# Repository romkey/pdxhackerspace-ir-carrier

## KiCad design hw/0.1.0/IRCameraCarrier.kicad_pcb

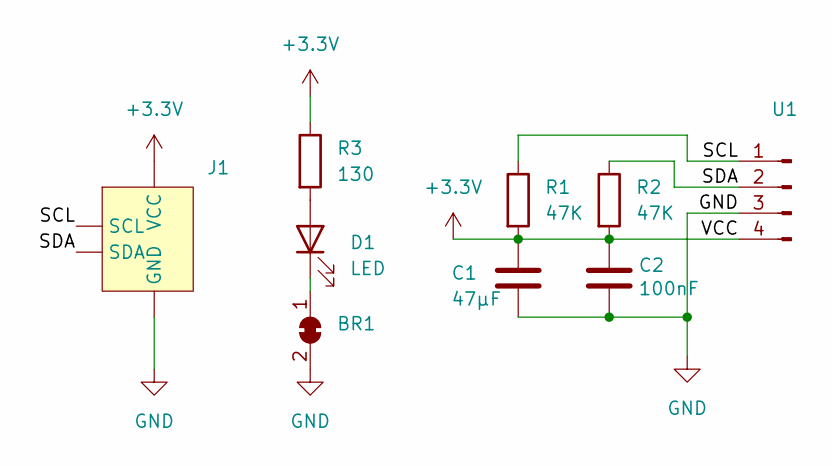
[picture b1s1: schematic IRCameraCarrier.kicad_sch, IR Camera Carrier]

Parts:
BR1: SolderJumper-2_P1.3mm_Bridged_RoundedPad1.0x1.5mm
C1: 47µF; C_1206_3216Metric_Pad1.33x1.80mm_HandSolder
C2: 100nF; C_1206_3216Metric_Pad1.33x1.80mm_HandSolder
D1: LED; LED_1206_3216Metric_Pad1.42x1.75mm_HandSolder
J1: JST_SH_SM04B-SRSS-TB_1x04-1MP_P1.00mm_Horizontal
R1, R2: 47K; R_1206_3216Metric_Pad1.30x1.75mm_HandSolder
R3: 130; R_1206_3216Metric_Pad1.30x1.75mm_HandSolder
U1: Conn_01x04_Pin; HTPA32x32d

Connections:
+3.3V: C1.1, C2.1, J1.2 (VCC), R1.2, R2.2, R3.1, U1.4
/SCL: J1.4 (SCL), R1.1, U1.1
/SDA: J1.3 (SDA), R2.1, U1.2
GND: BR1.2 (B), C1.2, C2.2, J1.1 (GND), U1.3
unnamed: BR1.1 (A), D1.1 (K)
unnamed: D1.2 (A), R3.2

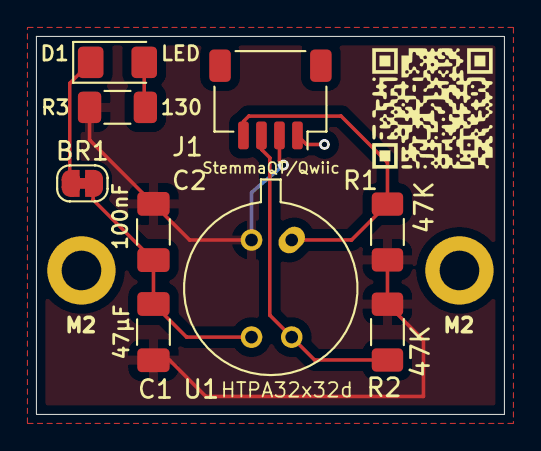
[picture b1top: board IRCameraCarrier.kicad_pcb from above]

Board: 2 copper layers, 26.0 x 21.0 mm, 9 parts (0 on the bottom side), 6 nets.

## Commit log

2024-08-12 added code of conduct and license
